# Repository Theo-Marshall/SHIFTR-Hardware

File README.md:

# SHIFTR 
A BLE to Direct Connect bridge for bike trainers using a WT32-ETH01 module based on ESP32. Increases connection stability and additionally adding Zwift "virtual shifting" functionality to any device supporting FE-C over BLE.

Currently tested with Garmin/Tacx NEO 2T and Vortex but should also work on other trainers supporting FE-C over BLE.

Tested bike trainer software so far:
- &#x2611; Zwift (Pass-through + virtual shifting mode)
- &#x2612; MyWhoosh (Pass-through mode only) -> Controllable not working with TACX Neo 2T as MyWhoosh probably relies on FTMS via DirCon. Maybe in an upcoming version I'll implement a FTMS emulator. May already work today with other trainers (supporting FTMS via BLE). 

Disclaimer: Even if everything is working fine this project is still work in progress. Feel free to provide feedback if you encounter any issues.

## Overview
Bike trainers heavily evolved over the last few years. Tacx (acquired by Garmin some years ago) is one of the market leaders producing bike trainers of a very high quality with special features like e.g. "Road Feeling" to simulate different road surfaces. 
Other vendors like Zwift came up with cool new features like "virtual shifting" using the "Zwift Cog" and a controller device (Zwift Click/Play) to have a non-mechanical shifting solution which is setting the gears via software that adjusts the resistance in the trainer. 
Wahoo came up with a technology called "Direct Connect" that allows the trainer devices to be connected via Ethernet (or even WiFi) instead of bluetooth to have a more stable connection.

While other vendors like e.g. Elite or JetBlack are very fast in implementing things like virtual shifting to their newer models Garmin is very slow and unresponsive when it comes to such feature requests. Probably also because they have their own ecosystem that competes with Zwift. 

Using Zwift for many years and owning a "Tacx Vortex" and a "Tacx Neo 2T" bike trainer I have been jealous of features like virtual shifting and the possibility to connect the trainer device via ethernet. So the idea for this project, SHIFTR, was born by having a device between Zwift and the Tacx supporting all this cool new functionality.

After many days and nights of searching the internet for a specification of the protocols I was only able to find small parts for "Direct Connect" that have already been reverse engineered by Roberto Viola in his [QDomyos-Zwift](https://github.com/cagnulein/qdomyos-zwift) project. The code helped me a lot to understand the protocol.
Unfortunately there was absolutely no information about the "virtual shifting" to be found. So a very long session of decompiling Zwift apps and sniffing BLE traffic between Zwift and capable trainers (which fortunately a friend had one of) started. It took some weeks but I was able to reverse engineer the used protocols.

As I wanted to have a convenient solution that doesn't require a special program or app to be started to have that functionality I decided to implement everything on an ESP32 microcontroller that already features WiFi and Bluetooth onboard and also optionally ethernet. The perfect module for that was the [WT32-ETH01](https://en.wireless-tag.com/product-item-2.html) module that comes with everything I needed. The device will be placed very close to the trainer in a 3D printed case that also has a place for a step down converter to be able to use the existing power supply from the trainer.

Now I have a great setup with a Garmin/Tacx NEO 2T with a Zwift Cog installed and communicating to Zwift via ethernet while still having the "Road Feeling" feature: 

This setup even works great with Zwift running on an Apple TV. Apple TV only supports two simultaneous bluetooth connections and those can now be used for the Zwift Play controllers while the trainer itself is being connected through ethernet.

## How it works
The SHIFTR is working in two modes, "Pass-through" and "Pass-through + virtual shifting":
### Pass-through mode
In this mode the SHIFTR just takes all services from the BLE trainer devices and provides them 1:1 via Direct Connect. It supports SIM and ERG mode as if the device would be connected via bluetooth.
### Pass-through + virtual shifting mode
This mode provides the pass through features as mentioned before and additionally offers a special Zwift service via Direct Connect that allows it to behave like a Zwift certified device offering virtual shifting, too. All necessary information like incline, bicycle and user weight, etc. are transmitted by Zwift and used for calculations. SIM and ERG mode are supported but of course virtual shifting only works in SIM mode.

Details about the virtual shifting function and calculations can be found [here](./VirtualShifting.md).

***Note***: Virtual shifting will be disabled if neither Zwift Play controllers nor a Zwift Click are connected which results in the standard SIM mode with a track resistance of 0%. Then you'd have to shift with your bike but with a Zwift Cog installed this doesn't make sense of course. If the controllers disconnect during a training then the fallback will be this normal SIM mode but as soon as the controller(s) are re-connected the virtual shifting will be enabled again.

## Needed hardware
- WT32-ETH01 ESP32 board (e.g. from [Amazon](https://www.amazon.de/WT32-ETH01-Embedded-Schnittstelle-Bluetooth-Entwicklungsplatine/dp/B0CW3DDWZ4))
- Step-Down converter 5-80V (the Tacx Neo supplies 48V) to 5V (e.g. from [Amazon](https://www.amazon.de/dp/B0CMC7Y3DJ))
- Y-Splitter for the Tacx power cable (e.g. from [Amazon](https://www.amazon.de/dp/B09FHHN9T5))
- Power connector for the case (e.g. from [Amazon](https://www.amazon.de/gp/product/B09PD6J4BN))
- 3D printed case that fits the WT32-ETH01. Luckily I was able to find a perfect match that also fits the step-down converter: [WT32-ETH01 Enclosure](https://www.thingiverse.com/thing:5621092)
- Two countersunk screws M2x7 to hold the lid on the case

## Hardware installation
- ***IMPORTANT***: Don't solder the pin headers that came with the WT32-ETH01. With the longer pins on the bottom side the module won't fit the case anymore.
- ***IMPORTANT #2***: Connect the step-down converter first to a power supply (e.g. the original one with 48V) and a multimeter and use a screwdriver to adjust the output voltage to 5V before connecting it to the WT32-ETH01 module!
- Use a standard USB<->TTL converter (e.g. with FTDI232 or similar). Make sure that it can provide **3,3V and not 5V** and connect as follows (see also pinout above):
  | Converter | -> | ETH01-EVO | 
  |-|-|-|
  | RX | -> | TXD |
  | TX | -> | RXD |
  | 3V3 | -> | 3V3 |
  | GND | -> | GND |

  It's best to use some breadboard jumper wires that can just be connected without soldering. Use a rubber band to hold them in contact.

  To start the WT32-ETH01 in boot mode it is necessary to connect "IO0" with GND and then to reset the board, shortly connect "EN" to GND for a quarter of a second.

## Software installation
- Open the project in [PlatformIO](https://platformio.org) and let it install the dependencies
- Connect the programmer and upload via the task wt32-eth01 -> Upload and Monitor
- Connect an ethernet cable and make sure a DHCP server exists in your network
- After a few seconds you should be able to see the IP address and the hostname (like e.g. "SHIFTR-123456.local") in the monitor log
- If you don't use the Ethernet interface you can also use the WiFi functionality. For that the device opens an AP with the device name (e.g. "SHIFTR-123456") and the password is the same but of course can be changed later. Please note that WiFi is provided by an external library called [IoTWebConf](https://github.com/prampec/IotWebConf) and is more or less untested
- After that you can configure the device and its network settings in the web interface on e.g. http://SHIFTR-123456.local
- The status page is accessible without credentials, the settings and firmware update pages need the username "admin" and the password is the configured AP password or just the device name (e.g. "SHIFTR-123456") as default. Note that both are case sensitive!
- Further updates can be made over ethernet or WiFi so you can disconnect the programming adapter now

## Finalization
- Finally you can solder some wires to the power connector to the step down module and from there to the WT32-ETH01. Then mount everything in the 3D printed case:

- Use the Y-Power-Splitter to connect the Tacx trainer and the device:

- Power the Trainer and go to the web interface
- Go to "Settings", select the trainer device and "Save"
- Make sure the "Virtual shifting" option is enabled if you want to use it. Virtual shifting only works in Zwift when a Zwift Click or Zwift Play controllers are connected. Otherwise it will fall back to the normal ERG and SIM modes
- In Zwift you need to connect to the "SHIFTR 123456" device instead of your old device now. Have fun!

## Thank you!
You've made it to the end, hopefully you'll have fun rebuilding the whole thing. Please tell me if you like it and if it works as expected.
In case of any questions feel free to contact me!

## Disclaimer
Please always check the documentation of the hardware you bought as there are sometimes small changes in pin assignments, voltage and so on. I don't take any liability for damages or injuries. Build this project at your own risk. The linked products and pages are for reference only. I don't get any money from the manufacturers or the (re)sellers.

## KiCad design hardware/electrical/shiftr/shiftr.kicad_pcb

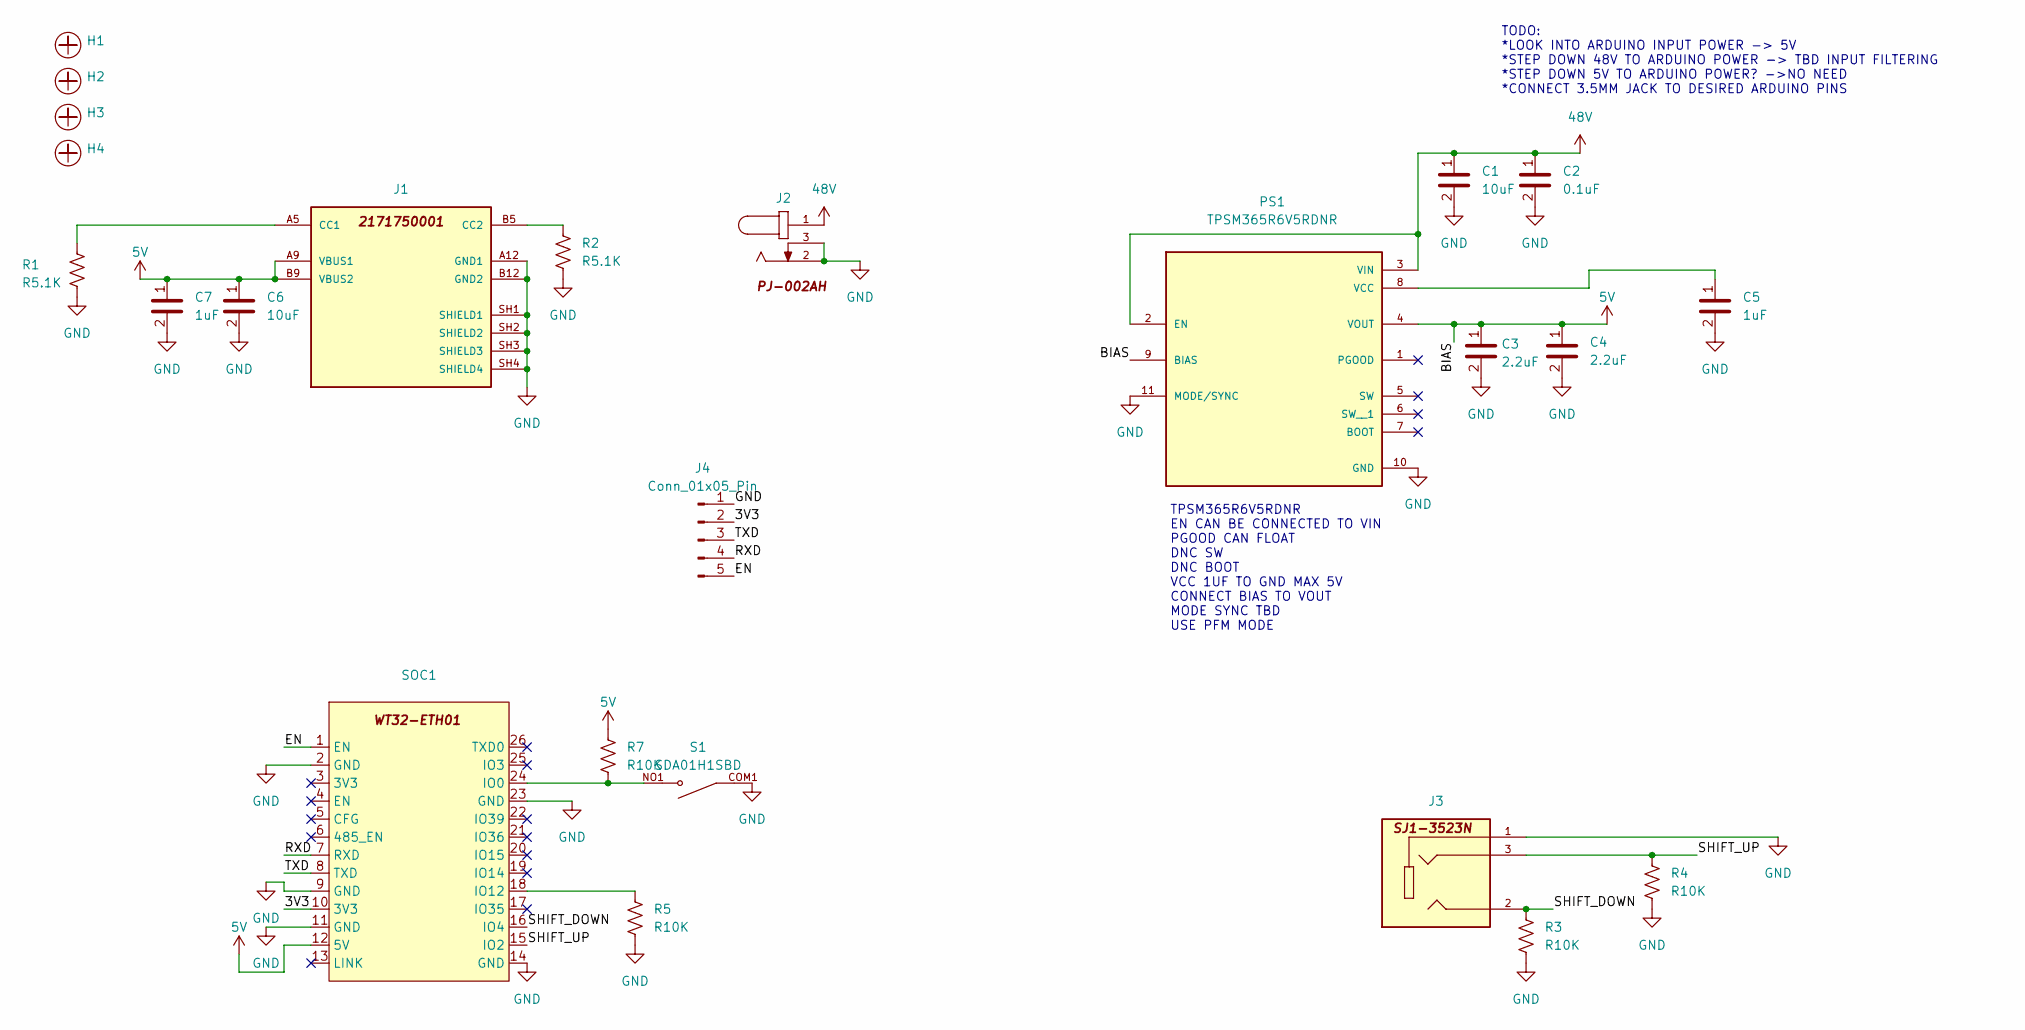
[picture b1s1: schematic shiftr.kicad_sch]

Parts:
C1, C6: 10uF; C_1210_3225Metric
C2: 0.1uF; C_1210_3225Metric
C3, C4: 2.2uF; C_1210_3225Metric
C5, C7: 1uF; C_0603_1608Metric
H1, H2, H3, H4: Hole-3mm
J1: 2171750001; MOLEX_2171750001; PARTREV A1
J2: PJ-002AH
J3: SJ1-3523N; CUI_SJ1-3523N; PARTREV 1.05
J4: Conn_01x05_Pin; PinHeader_1x05_P2.54mm_Vertical
PS1: TPSM365R6V5RDNR; PARTREV B
R1, R2: R5.1K; R_1206_3216Metric
R3, R4, R5, R7: R10K; R_1206_3216Metric
S1: SDA01H1SBD; SW_SDA01H1SBD; PARTREV 28 may 18
SOC1: WT32-ETH01

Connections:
5V: C3.1, C4.1, C6.1, C7.1, J1.A9 (VBUS1), J1.B9 (VBUS2), PS1.4 (VOUT), PS1.9 (BIAS), R7.1, SOC1.12 (5V)
48V: C1.1, C2.1, J2.1, PS1.2 (EN), PS1.3 (VIN), PS1.3_1, PS1.3_2
/3V3: J4.2, SOC1.10 (3V3)
/EN: J4.5, SOC1.1 (EN)
/RXD: J4.4, SOC1.7 (RXD)
/SHIFT_DOWN: J3.2, R3.1, SOC1.16 (IO4)
/SHIFT_UP: J3.3, R4.1, SOC1.15 (IO2)
/TXD: J4.3, SOC1.8 (TXD)
GND: C1.2, C2.2, C3.2, C4.2, C5.2, C6.2, C7.2, J1.A12 (GND1), J1.B12 (GND2), J1.SH1 (SHIELD1), J1.SH2 (SHIELD2), J1.SH3 (SHIELD3), J1.SH4 (SHIELD4), J2.2, J2.3, J3.1, J4.1, PS1.10 (GND), PS1.11 (MODE/SYNC), R1.2, R2.2, R3.2, R4.2, R5.2, S1.COM1, SOC1.2 (GND), SOC1.9 (GND), SOC1.11 (GND), SOC1.14 (GND), SOC1.23 (GND)
unnamed: J1.A5 (CC1), R1.1
unnamed: J1.B5 (CC2), R2.1
unnamed: C5.1, PS1.8 (VCC)
unnamed: R7.2, S1.NO1, SOC1.24 (IO0)
unnamed: R5.1, SOC1.18 (IO12)

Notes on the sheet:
TODO: *LOOK INTO ARDUINO INPUT POWER -> 5V *STEP DOWN 48V TO ARDUINO POWER -> TBD INPUT FILTERING *STEP DOWN 5V TO ARDUINO POWER? ->NO NEED *CONNECT 3.5MM JACK TO DESIRED ARDUINO PINS
TPSM365R6V5RDNR EN CAN BE CONNECTED TO VIN PGOOD CAN FLOAT DNC SW DNC BOOT VCC 1UF TO GND MAX 5V CONNECT BIAS TO VOUT MODE SYNC TBD USE PFM MODE

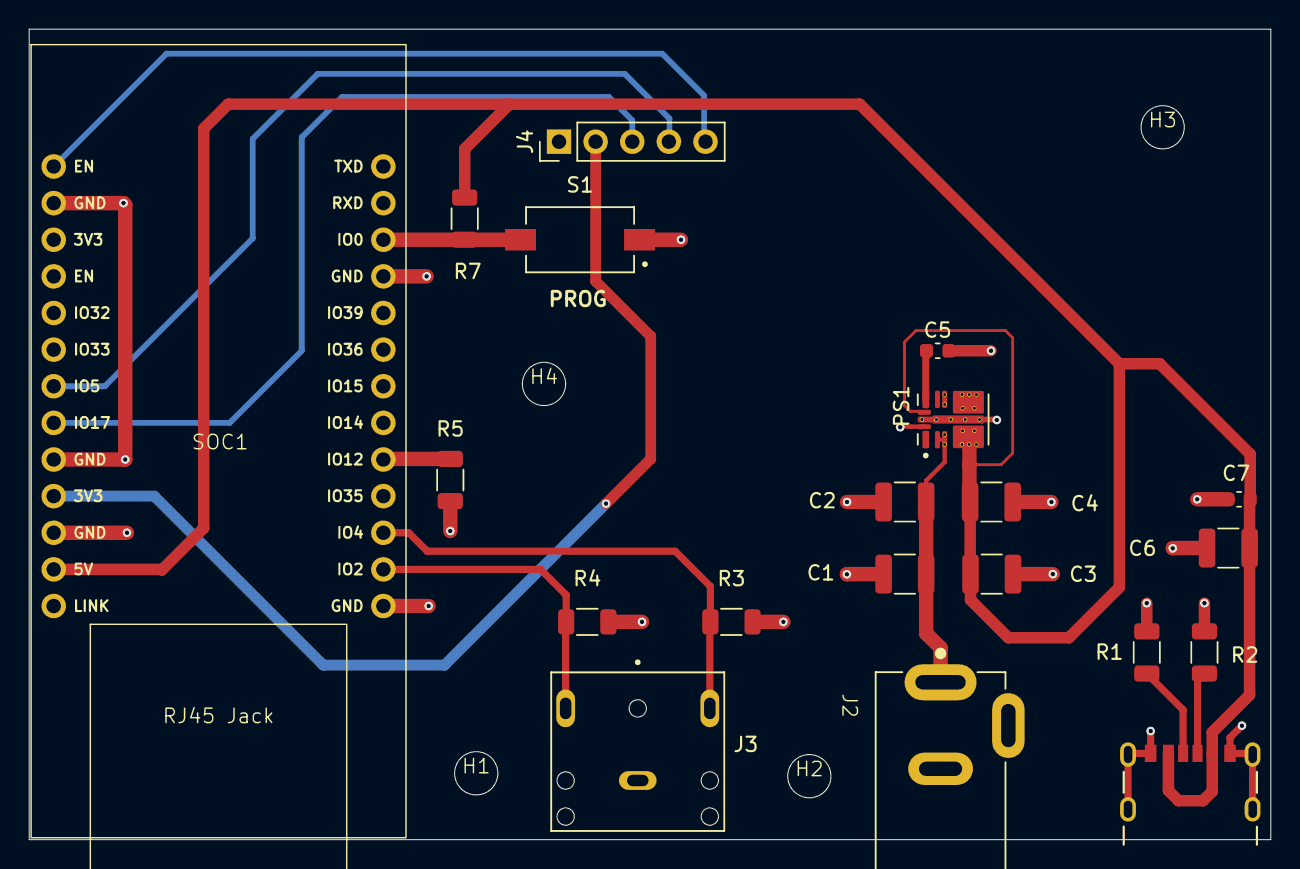
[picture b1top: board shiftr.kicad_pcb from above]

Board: 2 copper layers, 86.1 x 56.2 mm, 24 parts (0 on the bottom side), 14 nets.

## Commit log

2024-10-14 chore: initial commit
2024-10-20 feat!: add DirCon message handling
2024-10-20 feat!: add central DirCon service registry
2024-10-21 fix: repair service advertising and handling
2024-10-23 chore: start refactor
2024-10-23 feat: add ServiceManager
2024-10-24 feat: add BLEDeviceManager
2024-10-24 fix: repair BLE/BT classes
2024-10-24 feat: add BLE client connection manager
2024-10-28 feat: add DirConManager
2024-10-28 feat: add subscription callbacks
2024-10-31 feat: add service callbacks
2024-10-31 chore: clean up old code
2024-11-01 feat: add file based web server
2024-11-01 feat: add bidirectional BLE/DirCon processing
2024-11-01 chore: code cleanup
2024-11-01 feat: make web interface pretty
2024-11-03 feat(web): add connection status
2024-11-03 feat(DirCon): add internal notifications
2024-11-04 feat: add virtual shifting for Zwift
2024-11-05 chore: add debugging
2024-11-05 fix: repair DirCon notification handling
2024-11-05 chore: remove unnecessary logs
2024-11-06 feat: add ERG and SIM mode to internal characteristics
2024-11-06 chore: add CPS and FE-C docs
2024-11-06 feat(web): add device settings page
2024-11-06 chore: add documentation
2024-11-06 feat(web): add settings handling and usage
2024-11-07 fix: search for checksum errors
2024-11-07 fix: repair BLE write
2024-11-08 feat: add SettingsManager
2024-11-08 feat: add status messages to main services
2024-11-08 feat(web): use status messages in UI
2024-11-08 chore: cleanup
2024-11-08 fix: remove wrong named files
2024-11-08 fix: re-add correct named files
2024-11-08 chore: more cleanup
2024-11-08 feat: add SIM and ERG mode with virtual shifting
2024-11-08 fix: add unsigned LEB128 decoding
2024-11-09 feat: test new virtual shifting variant
2024-11-10 feat: add another virtual shifting variant, working good
2024-11-10 feat: add bicycle and user weight handling
2024-11-10 chore: readme update
2024-11-10 chore: version bump
2024-11-11 feat!: add better virtual shifting
2024-11-12 fix: add debugging to new virtual shifting
2024-11-12 chore: add more debug logs and tests
2024-11-13 feat: use power and cadence from FE-C
2024-11-13 feat: add new virtual shifting calculation with FE-C speed information
2024-11-13 fix: correct calculation of negative total force
2024-11-14 fix: update documentation
2024-11-14 chore: cleanup code
2024-11-14 feat: add better calculation and calculation class
2024-11-15 feat: add gear ratio to settings, add new resistance calculation
2024-11-15 fix: remove signed LEB128, add special signed support, repair calculations
2024-11-15 chore: version bump, cleanup
2024-11-16 fix: use gear ratio in reverse calculations
2024-11-16 feat: add GitHub Actions build script
2024-11-16 feat: add CI workflow
2024-11-16 fix: update workflow branch
2024-11-16 fix: use correct versions in CI workflow
2024-11-16 feat: add CI status badge to readme
2024-11-16 fix: correct calculation mistake, make track resistance not default
2024-11-16 feat: add NOTICE.txt and license badge
2024-11-17 feat: add target power virtual shifting mode
2024-11-17 feat: add internal speed calculation, check power underrun
2024-11-17 feat: new versioning and CI scripts
2024-11-17 chore: documentation cleanup
2024-11-18 feat: new CI workflow
2024-11-18 fix: copy ota.ini in CI build
2024-11-18 fix: adjust CI build
2024-11-18 fix: repair naming of release file
2024-11-18 fix: filename version with dots instead of dashes
2024-11-18 feat: adjust CI for 'develop' branch
2024-11-18 feat: make "target power" mode the default
2024-11-18 fix: correct version in local builds
2024-11-18 fix: repair version major number from tag string
2024-11-18 fix: repair broken formulas in readme
2024-11-24 feat: add authentication to settings and firmware upgrade page
2024-11-24 feat!: remove OTA profile and functionality
2024-12-07 fix(local): use correct tag line split
2024-12-07 feat(targetpower): use different calculation in target power mode
2025-02-06 refactor: move calculations to lib folder
2025-02-06 feat: add native testing for calculations
2025-02-06 fix: revert change for calculation in target power mode
2025-02-06 fix: add default gear ratio in target power mode
2025-02-07 feat: add test defaults
2025-02-07 feat: add smoothing for grade
2025-02-07 feat(web): add grade smoothing setting to web interface
2025-02-07 fix: update workflow script with new upload-artifact v4
2025-02-11 fix: correct msg_id and bicycle weight parameter
2025-02-11 feat: experiments with FE-C parameters
2025-02-11 feat: improve calculations and logging
2025-02-12 feat(logger): more improvements and compatibility with esp logging
2025-02-12 feat(logger): make log level settable in runtime with defaults
2025-02-12 feat(trackresistance): add new calculation with better ride feeling
2025-02-13 feat(web): add difficulty level
2025-02-13 feat(basicresistance, targetpower): add new calculation with better ride feeling
2025-02-14 feat(basicresistance): add difficulty level and calculate speed instead of measured value
2025-02-15 fix: correct usage of speed and resistances in calculations
2025-02-15 feat(trackresistance, targetpower): add difficulty level
2025-02-16 feat: make basic resistance mode the default
2025-02-16 fix(targetpower): use physical gear ratio for speed and power calculation
2025-02-16 feat: update README and move virtual shifting details to separate markdown file
2025-02-17 feat(docs): add FTMS documentation
2025-02-17 feat(dircon): add FTMS emulation with setting in web interface
2025-02-17 feat: update readme with FTMS emulation information
2025-02-22 feat: add gear control via gpio and web interface
2025-02-26 feat: add "zwiftless" virtual shifting
2025-02-27 add electrical project, ignore backups
2025-02-27 add WT32-ETH01 footprint"
2025-02-27 add WT32-ETH01 symbol
2025-02-28 fix: update resistance on every shift instead of only after software request
2025-02-28 feat: retrieve maximum resistance after connection of trainer
2025-03-04 add wth symbol to schematic
2025-03-04 add barrel connector to sch and pcb lib
2025-03-04 add audio jack sch and pcb
2025-03-04 add usb c connector sch and pcb lib
2025-03-04 add 5.1kohm resistor sch
2025-03-08 flesh out more of the 48v->5v conversion
2025-03-14 add shift button nets, pull down resistors
2025-03-14 route traces
2025-03-16 finish up routing, wt32 now on headers
2025-03-16 add programming pinheader
2025-03-19 update some traces

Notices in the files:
README.md:
License: GPL v3
